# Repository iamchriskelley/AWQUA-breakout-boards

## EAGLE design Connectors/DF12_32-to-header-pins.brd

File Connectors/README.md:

#Connectors

###DF12_32
The DF12_32 is a 0.5mm Pitch SMT Board to Board Connector, useful for squeezing lots of connections into a small package. It is available at [Mouser](http://www.mouser.com/ProductDetail/Hirose-Connector/DF12B30-32DP-05V86/?qs=sGAEpiMZZMvffgRu4KC1Rw0uA%252bB%2fcqq%2f4q0JSgefN%252bw%3d) and as of this writing costs $1.03/ea (Q10).

###USBMICRO-10118193-0001LF
The USBMICRO-10118193-0001LF is a female SMD USBMicro connector with through-hole anchoring to help keep the part securely attached to the board. It is available at [Mouser](http://www.mouser.com/ProductDetail/FCI/10118193-0001LF/?qs=%2fha2pyFadujdGYiRLwYbSAiZv7CvK3RU%252bw5BMdkZ%2f8U%3d) and as of this writing costs $0.316/ea (Q10). 

###USBMICRO-DX4R005JJ2
The USBMICRO-DX4R005JJ2 is a female SMD USBMicro connector with through-hole anchoring to help keep the part securely attached to the board. It is available at [Mouser](http://www.mouser.com/ProductDetail/JAE-Electronics/DX4R005JJ2R1800/?qs=%2fha2pyFadugU0xC23dAUHX6C4DwqBJUbZgQnVMZlkaX%2fumUbOrM6PA%3d%3d) and as of this writing costs $0.618/ea (Q10).

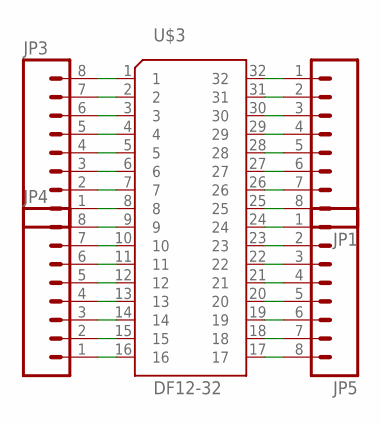
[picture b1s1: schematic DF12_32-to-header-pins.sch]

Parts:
JP1, JP3, JP4, JP5: M081X08; 1X08
U$3: DF12-32

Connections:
unnamed: JP4.1, U$3.16
unnamed: JP4.2, U$3.15
unnamed: JP4.3, U$3.14
unnamed: JP4.4, U$3.13
unnamed: JP4.5, U$3.12
unnamed: JP4.6, U$3.11
unnamed: JP4.7, U$3.10
unnamed: JP4.8, U$3.9
unnamed: JP3.1, U$3.8
unnamed: JP3.2, U$3.7
unnamed: JP3.3, U$3.6
unnamed: JP3.4, U$3.5
unnamed: JP3.5, U$3.4
unnamed: JP3.6, U$3.3
unnamed: JP3.7, U$3.2
unnamed: JP3.8, U$3.1
unnamed: JP1.1, U$3.32
unnamed: JP1.2, U$3.31
unnamed: JP1.3, U$3.30
unnamed: JP1.4, U$3.29
unnamed: JP1.5, U$3.28
unnamed: JP1.6, U$3.27
unnamed: JP1.7, U$3.26
unnamed: JP1.8, U$3.25
unnamed: JP5.1, U$3.24
unnamed: JP5.2, U$3.23
unnamed: JP5.3, U$3.22
unnamed: JP5.4, U$3.21
unnamed: JP5.5, U$3.20
unnamed: JP5.6, U$3.19
unnamed: JP5.7, U$3.18
unnamed: JP5.8, U$3.17

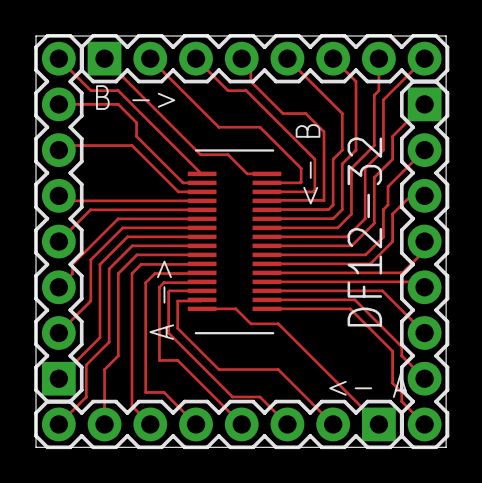
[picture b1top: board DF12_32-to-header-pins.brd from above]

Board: 2 copper layers, 22.8 x 22.9 mm, 5 parts (0 on the bottom side), 32 nets.

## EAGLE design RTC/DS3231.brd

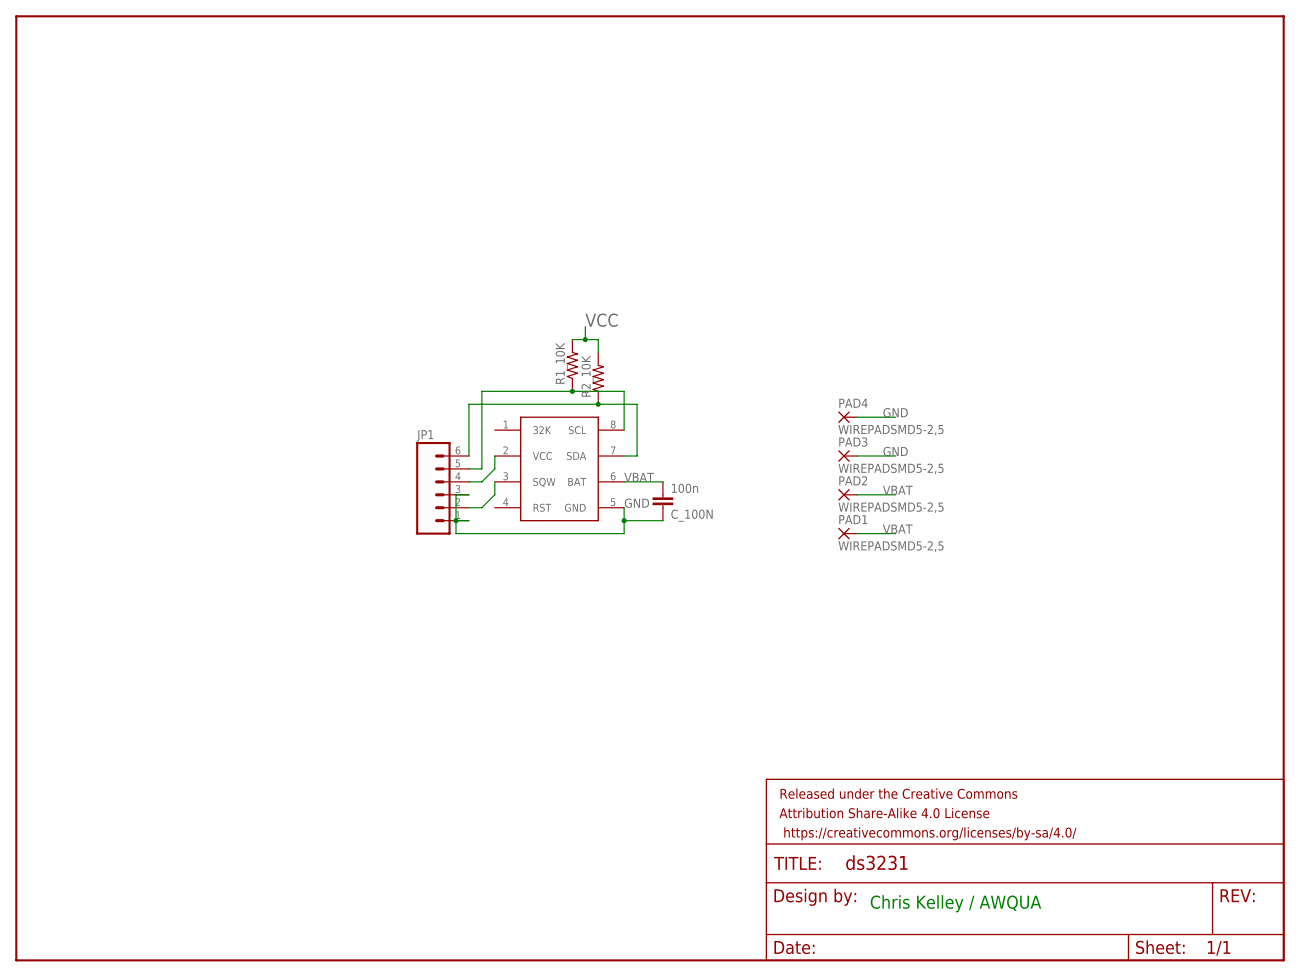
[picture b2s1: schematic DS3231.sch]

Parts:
C_100N: 100n; 0603-CAP
DS3231: DS3231M
FRAME1: FRAME-LETTER; CREATIVE_COMMONS
JP1: M06SILK_FEMALE_PTH; 1X06
PAD1, PAD2, PAD3, PAD4: WIREPADSMD5-2,5; 5-2,5
R1_10K, R2_10K: RESISTOR0603-RES; 0603-RES

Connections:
GND: C_100N.1, DS3231.5 (GND), JP1.1, JP1.3, PAD3.1, PAD4.1
SCL: DS3231.8 (SCL), JP1.5, R1_10K.1
SDA: DS3231.7 (SDA), JP1.6, R2_10K.1
SQW: DS3231.3 (SQW), JP1.2
VBAT: C_100N.2, DS3231.6 (BAT), PAD1.1, PAD2.1
VCC: DS3231.2 (VCC), JP1.4, R1_10K.2, R2_10K.2

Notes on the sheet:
Chris Kelley / AWQUA

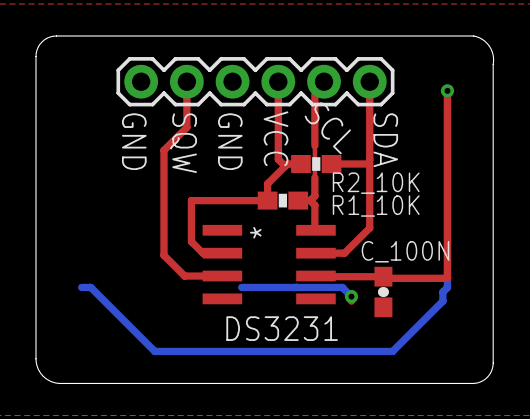
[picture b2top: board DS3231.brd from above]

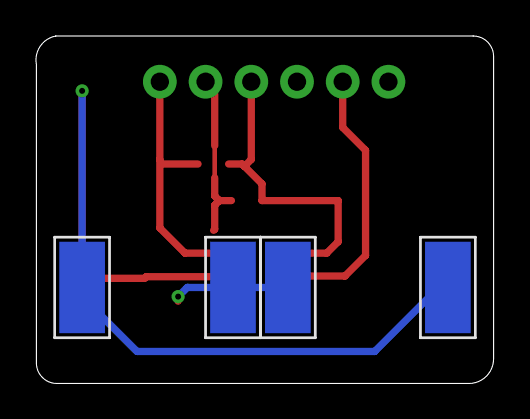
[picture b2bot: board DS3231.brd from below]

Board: 2 copper layers, 25.4 x 19.3 mm, 10 parts (4 on the bottom side), 6 nets.

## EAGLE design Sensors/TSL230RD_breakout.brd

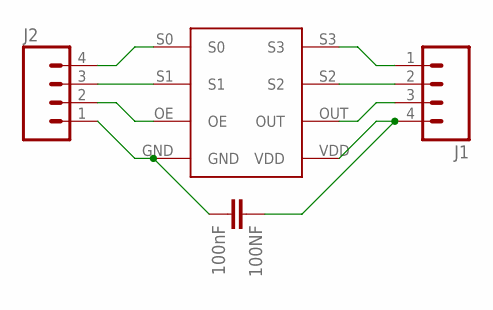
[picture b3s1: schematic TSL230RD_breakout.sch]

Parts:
100NF: 100nF; 0603-CAP
J1, J2: M04PTH; 1X04
U$1: TSL230RDSMD; TSL230RD

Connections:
unnamed: J2.4, U$1.S0
unnamed: J2.3, U$1.S1
unnamed: J2.2, U$1.OE
unnamed: 100NF.2, J2.1, U$1.GND
unnamed: J1.1, U$1.S3
unnamed: J1.2, U$1.S2
unnamed: J1.3, U$1.OUT
unnamed: 100NF.1, J1.4, U$1.VDD

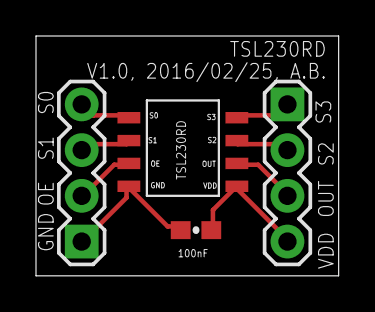
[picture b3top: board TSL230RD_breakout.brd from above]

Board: 2 copper layers, 16.8 x 13.3 mm, 4 parts (0 on the bottom side), 8 nets.

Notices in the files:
parts and their libraries:
SparkFun-Connectors: Licensing: CC v3.0 Share-Alike You are welcome to use this library for commercial purposes.
SparkFun-Aesthetics: Licensing: Creative Commons ShareAlike 4.0 International - https://creativecommons.org/licenses/by-sa/4.0
SparkFun-Aesthetics: Released under the Creative Commons
